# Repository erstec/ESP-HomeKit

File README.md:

# ESP-HomeKit
Espressif ESP-based HomeKit Controller

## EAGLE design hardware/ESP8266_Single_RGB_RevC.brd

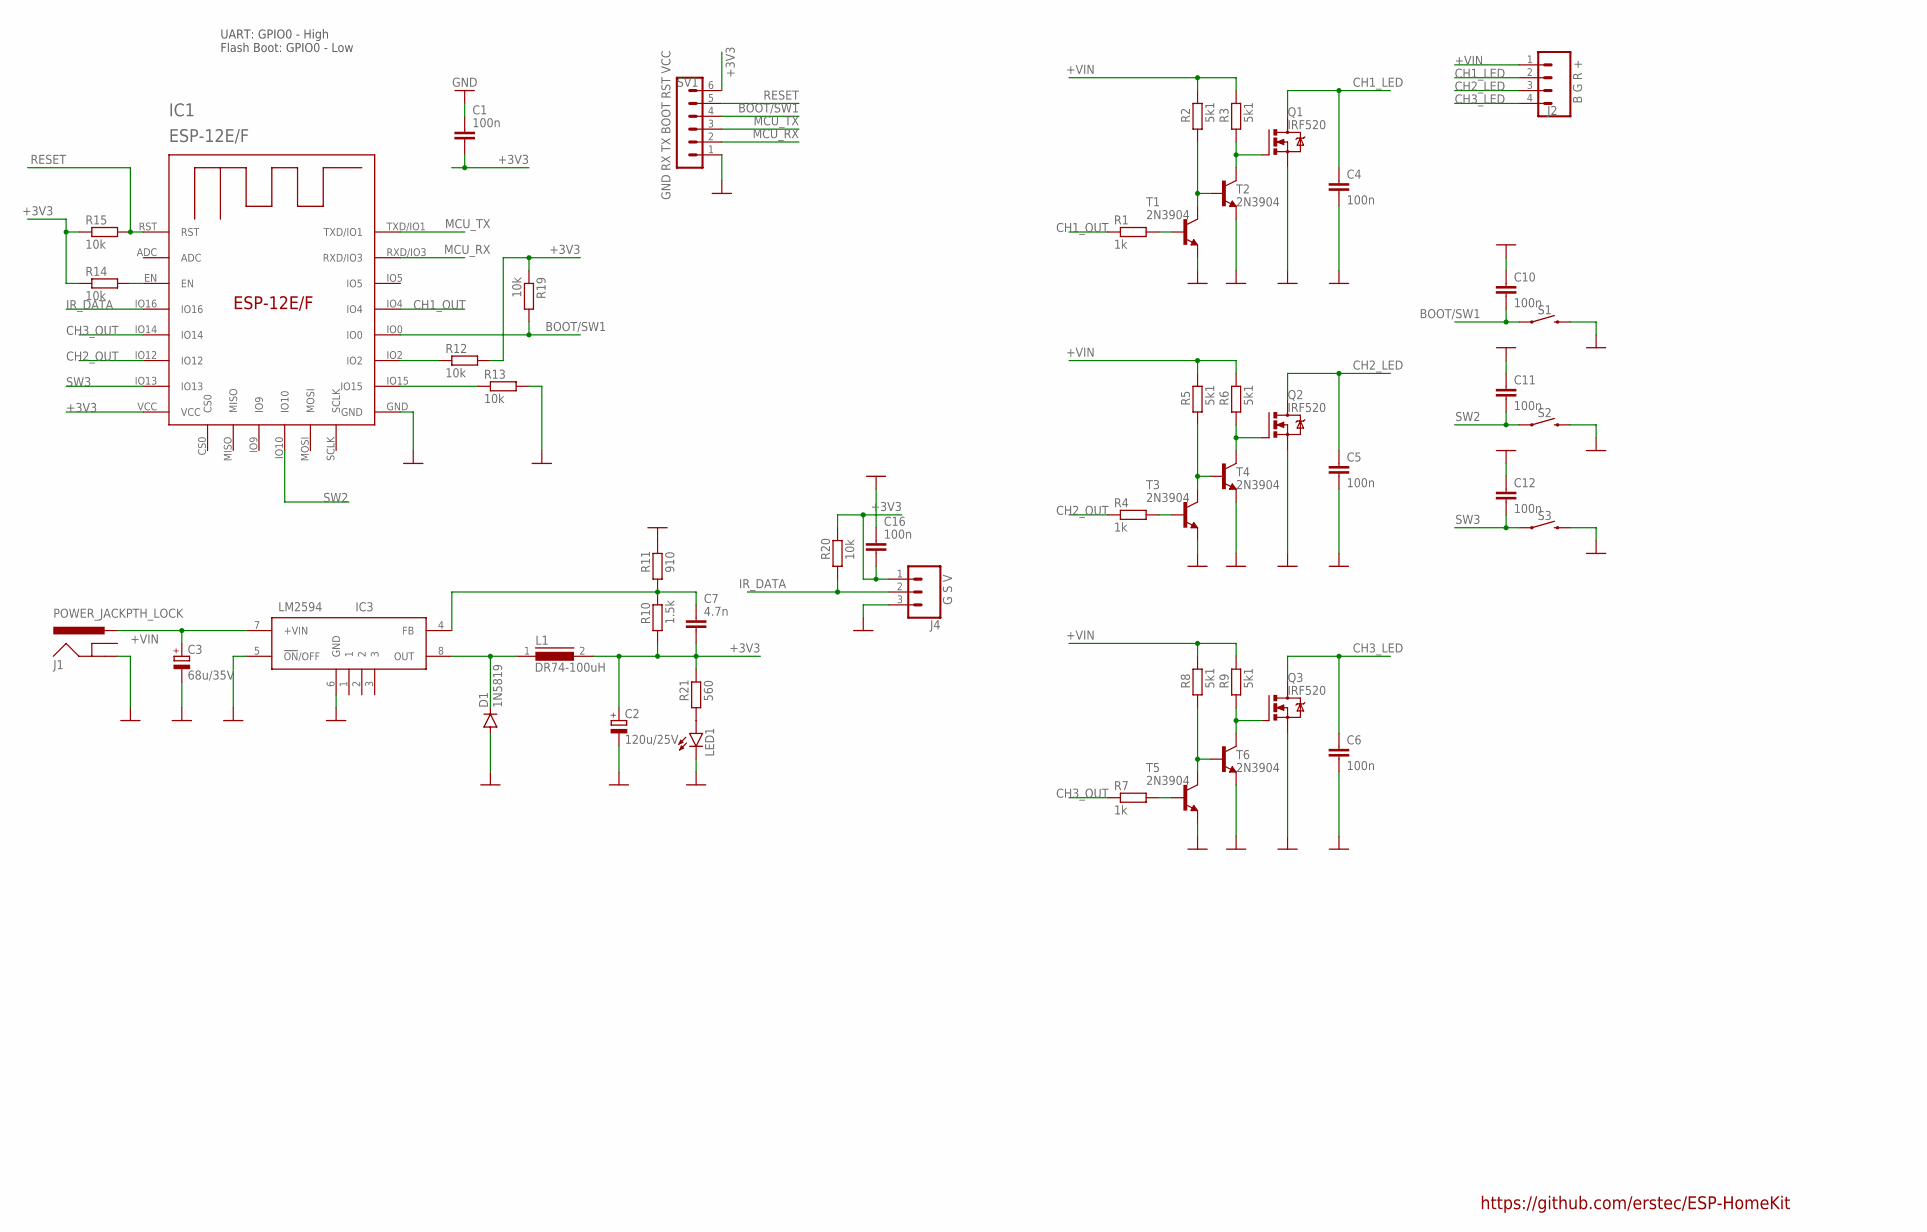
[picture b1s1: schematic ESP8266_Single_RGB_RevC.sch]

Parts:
C1, C4, C5, C6, C10, C11, C12, C16: 100n; C050-024X044
C2: 120u/25V; E2,5-6E
C3: 68u/35V; E2,5-6
C7: 4.7n; C0805
D1: 1N5819; DO41-7.6
IC1: ESP-12E/F; ESP-12E
IC3: LM2594; TSOP8
J1: POWER_JACKPTH_LOCK; POWER_JACK_PTH_LOCK
J2: B G R +; SCREWTERMINAL-3.5MM-4_LOCK
J4: G S V; SCREWTERMINAL-3.5MM-3_LOCK.007S
L1: DR74-100uH; DR74
LED1: LED5MM
Q1, Q2, Q3: IRF520; TO220BV
R1, R4, R7: 1k; 0204/7
R2, R3, R5, R6, R8, R9: 5k1; 0204/7
R10: 1.5k; M0805
R11: 910; R0805
R12, R13, R14, R15, R19, R20: 10k; 0204/7
R21: 560; 0204/7
S1, S2, S3: MOMENTARY-SWITCH-SPST-PTH-6.0MM; TACTILE_SWITCH_PTH_6.0MM
SV1: GND RX TX BOOT RST VCC; MA06-1
T1, T2, T3, T4, T5, T6: 2N3904; TO92-EBC

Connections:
+3V3: C1.2, C2.+, C7.2, C16.2, IC1.VCC, J4.1, L1.2, R10.1, R12.2, R14.1, R15.1, R19.1, R20.2, R21.2, SV1.6
+VIN: C3.+, IC3.7 (+VIN), J1.PWR, J2.1, R2.2, R3.2, R5.2, R6.2, R8.2, R9.2
BOOT/SW1: C10.2, IC1.IO0, R19.2, S1.1, SV1.4
CH1_LED: C4.1, J2.2, Q1.D
CH1_OUT: IC1.IO4, R1.1
CH2_LED: C5.1, J2.3, Q2.D
CH2_OUT: IC1.IO12, R4.1
CH3_LED: C6.1, J2.4, Q3.D
CH3_OUT: IC1.IO14, R7.1
GND: C1.1, C2.-, C3.-, C4.2, C5.2, C6.2, C10.1, C11.1, C12.1, C16.1, D1.A, IC1.GND, IC3.5 (!ON!/OFF), IC3.6 (GND), J1.GND, J4.3, LED1.K (C), Q1.S, Q2.S, Q3.S, R11.2, R13.2, S1.3 (2), S2.3 (2), S3.3 (2), SV1.1, T1.E, T2.E, T3.E, T4.E, T5.E, T6.E
IR_DATA: IC1.IO16, J4.2, R20.1
MCU_RX: IC1.RXD/IO3, SV1.2
MCU_TX: IC1.TXD/IO1, SV1.3
unnamed: R2.1, T1.C, T2.B
unnamed: R1.2, T1.B
unnamed: LED1.A, R21.1
unnamed: Q1.G, R3.1, T2.C
unnamed: C7.1, IC3.4 (FB), R10.2, R11.1
unnamed: R5.1, T3.C, T4.B
unnamed: R4.2, T3.B
unnamed: Q2.G, R6.1, T4.C
unnamed: D1.C, IC3.8 (OUT), L1.1
unnamed: R8.1, T5.C, T6.B
unnamed: R7.2, T5.B
unnamed: Q3.G, R9.1, T6.C
unnamed: IC1.IO2, R12.1
unnamed: IC1.IO15, R13.1
unnamed: IC1.EN, R14.2
RESET: IC1.RST, R15.2, SV1.5
SW2: C11.2, IC1.IO10, S2.1
SW3: C12.2, IC1.IO13, S3.1

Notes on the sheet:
UART: GPIO0 - High Flash Boot: GPIO0 - Low
https://github.com/erstec/ESP-HomeKit

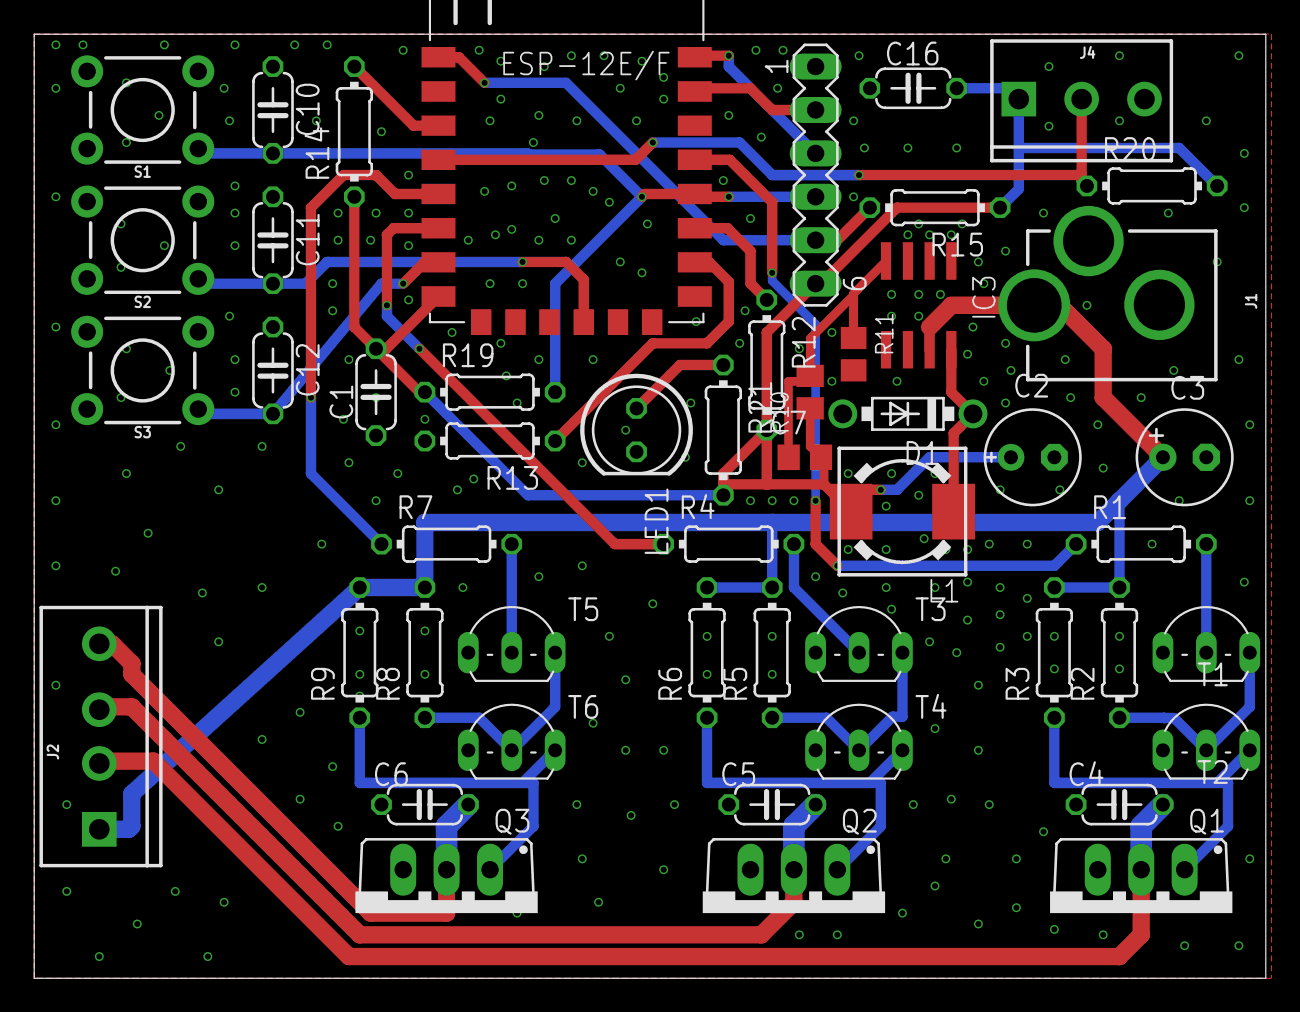
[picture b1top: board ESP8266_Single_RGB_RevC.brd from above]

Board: 2 copper layers, 72.1 x 55.2 mm, 50 parts (0 on the bottom side), 31 nets.

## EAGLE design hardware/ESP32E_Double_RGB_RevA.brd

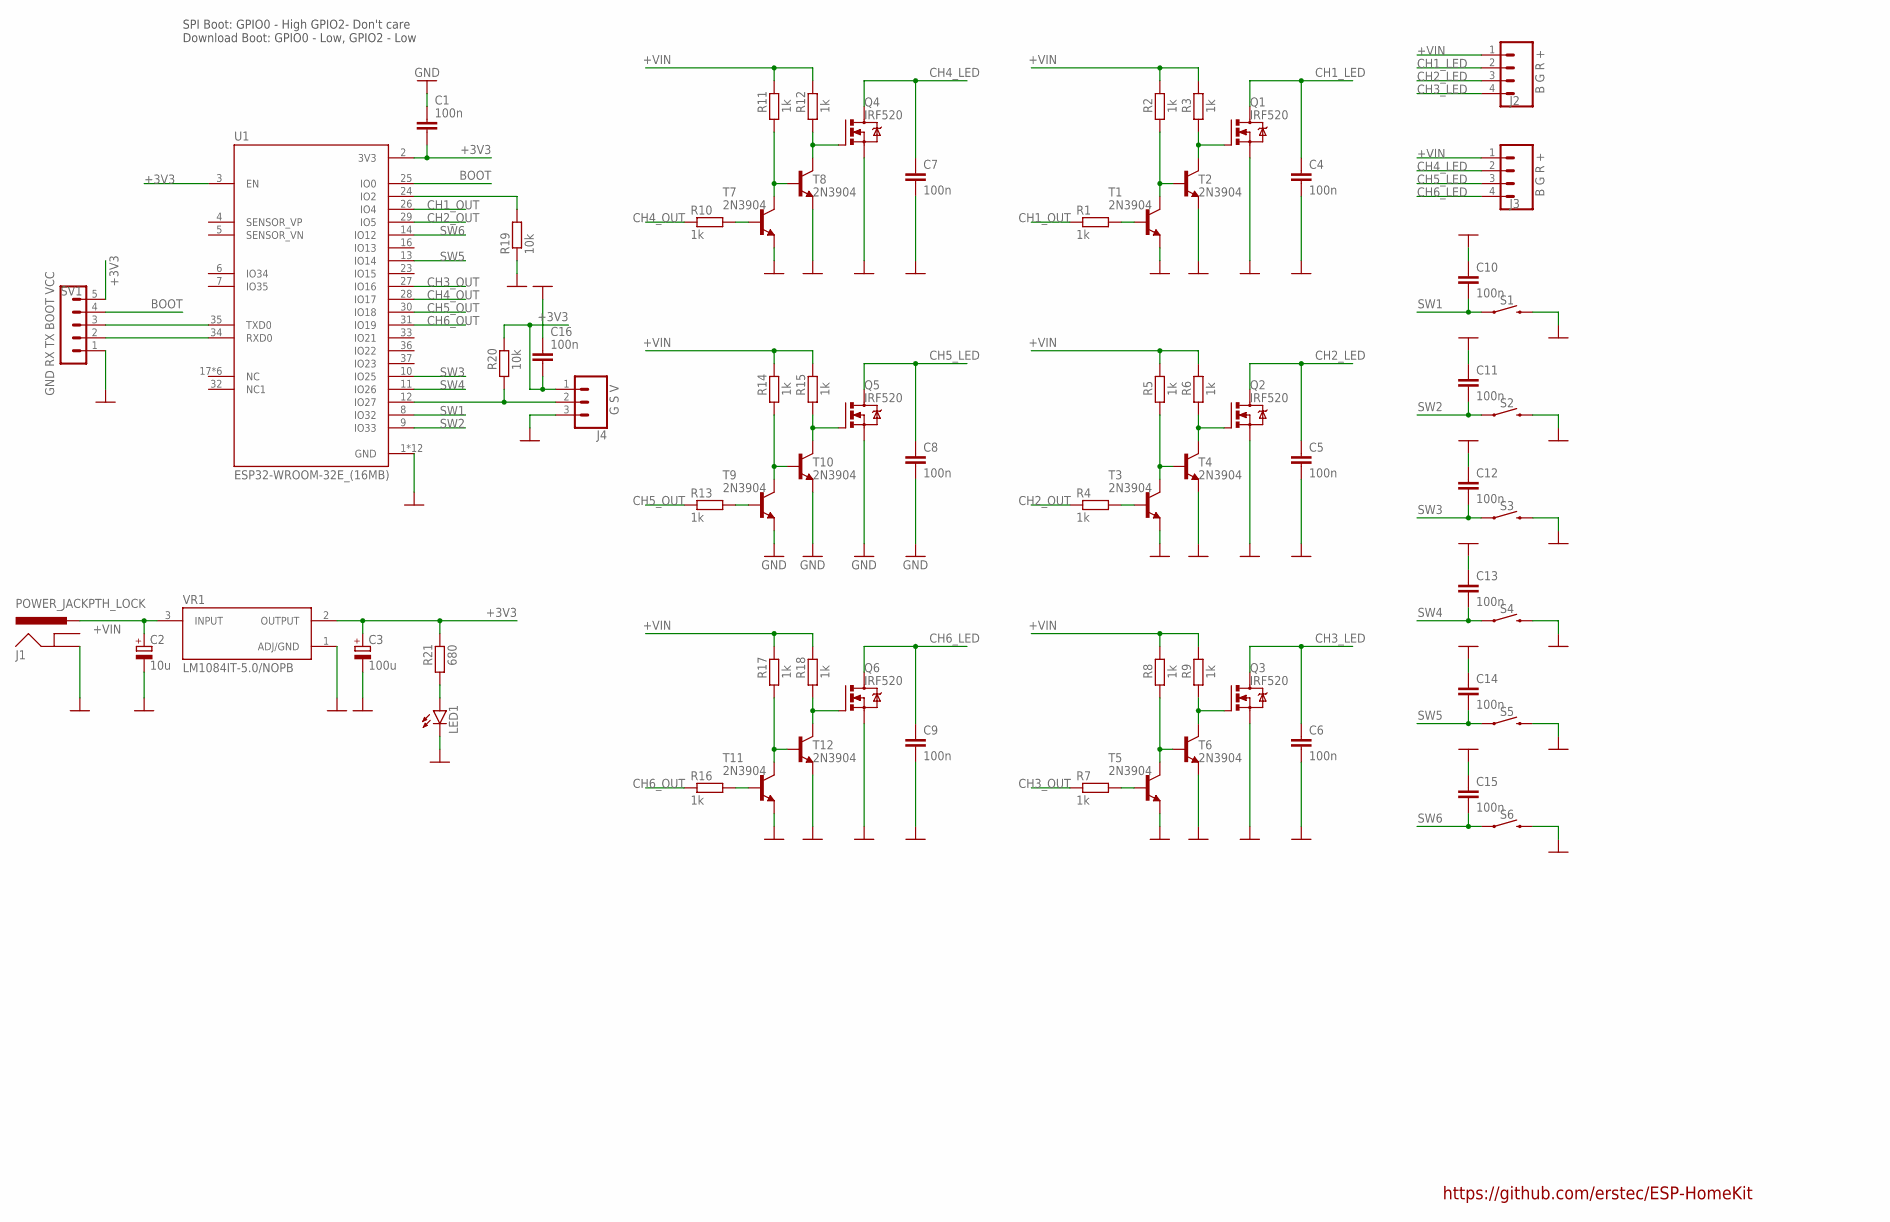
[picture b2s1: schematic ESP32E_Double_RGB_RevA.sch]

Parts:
C1, C4, C5, C6, C7, C8, C9, C10, C11, C12, C13, C14, C15, C16: 100n; C025-024X044
C2: 10u; E2,5-6E
C3: 100u; E2,5-6
J1: POWER_JACKPTH_LOCK; POWER_JACK_PTH_LOCK
J2, J3: B G R +; SCREWTERMINAL-3.5MM-4_LOCK
J4: G S V; SCREWTERMINAL-3.5MM-3_LOCK.007S
LED1: LED5MM
Q1, Q2, Q3, Q4, Q5, Q6: IRF520; TO220BV
R1, R2, R3, R4, R5, R6, R7, R8, R9, R10, R11, R12, R13, R14, R15, R16, R17, R18: 1k; 0207/10
R19, R20: 10k; 0207/10
R21: 680; 0207/10
S1, S2, S3, S4, S5, S6: MOMENTARY-SWITCH-SPST-PTH-6.0MM; TACTILE_SWITCH_PTH_6.0MM
SV1: GND RX TX BOOT VCC; MA05-1
T1, T2, T3, T4, T5, T6, T7, T8, T9, T10, T11, T12: 2N3904; TO92
U1: ESP32-WROOM-32E_(16MB); XCVR_ESP32-WROOM-32E_(16MB)
VR1: LM1084IT-5.0/NOPB; TO254P1054X470X1955-3

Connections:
+3V3: C1.2, C3.+, C16.2, J4.1, R20.2, R21.2, SV1.5, U1.2 (3V3), U1.3 (EN), VR1.2 (OUTPUT)
+VIN: C2.+, J1.PWR, J2.1, J3.1, R2.2, R3.2, R5.2, R6.2, R8.2, R9.2, R11.2, R12.2, R14.2, R15.2, R17.2, R18.2, VR1.3 (INPUT)
BOOT: SV1.4, U1.25 (IO0)
CH1_LED: C4.1, J2.2, Q1.D
CH1_OUT: R1.1, U1.26 (IO4)
CH2_LED: C5.1, J2.3, Q2.D
CH2_OUT: R4.1, U1.29 (IO5)
CH3_LED: C6.1, J2.4, Q3.D
CH3_OUT: R7.1, U1.27 (IO16)
CH4_LED: C7.1, J3.2, Q4.D
CH4_OUT: R10.1, U1.28 (IO17)
CH5_LED: C8.1, J3.3, Q5.D
CH5_OUT: R13.1, U1.30 (IO18)
CH6_LED: C9.1, J3.4, Q6.D
CH6_OUT: R16.1, U1.31 (IO19)
GND: C1.1, C2.-, C3.-, C4.2, C5.2, C6.2, C7.2, C8.2, C9.2, C10.1, C11.1, C12.1, C13.1, C14.1, C15.1, C16.1, J1.GND, J4.3, LED1.K (C), Q1.S, Q2.S, Q3.S, Q4.S, Q5.S, Q6.S, R19.1, S1.3 (2), S2.3 (2), S3.3 (2), S4.3 (2), S5.3 (2), S6.3 (2), SV1.1, T1.3 (E), T2.3 (E), T3.3 (E), T4.3 (E), T5.3 (E), T6.3 (E), T7.3 (E), T8.3 (E), T9.3 (E), T10.3 (E), T11.3 (E), T12.3 (E), U1.1 (GND), U1.15 (GND), U1.38 (GND), U1.39_1 (GND), U1.39_2 (GND), U1.39_3 (GND), U1.39_4 (GND), U1.39_5 (GND), U1.39_6 (GND), U1.39_7 (GND), U1.39_8 (GND), U1.39_9 (GND), VR1.1 (ADJ/GND)
unnamed: R2.1, T1.1 (C), T2.2 (B)
unnamed: R1.2, T1.2 (B)
unnamed: LED1.A, R21.1
unnamed: Q1.G, R3.1, T2.1 (C)
unnamed: J4.2, R20.1, U1.12 (IO27)
unnamed: SV1.2, U1.34 (RXD0)
unnamed: SV1.3, U1.35 (TXD0)
unnamed: R5.1, T3.1 (C), T4.2 (B)
unnamed: R4.2, T3.2 (B)
unnamed: Q2.G, R6.1, T4.1 (C)
unnamed: R8.1, T5.1 (C), T6.2 (B)
unnamed: R7.2, T5.2 (B)
unnamed: Q3.G, R9.1, T6.1 (C)
unnamed: R11.1, T7.1 (C), T8.2 (B)
unnamed: R10.2, T7.2 (B)
unnamed: Q4.G, R12.1, T8.1 (C)
unnamed: R14.1, T9.1 (C), T10.2 (B)
unnamed: R13.2, T9.2 (B)
unnamed: Q5.G, R15.1, T10.1 (C)
unnamed: R17.1, T11.1 (C), T12.2 (B)
unnamed: R16.2, T11.2 (B)
unnamed: Q6.G, R18.1, T12.1 (C)
unnamed: R19.2, U1.24 (IO2)
SW1: C10.2, S1.1, U1.8 (IO32)
SW2: C11.2, S2.1, U1.9 (IO33)
SW3: C12.2, S3.1, U1.10 (IO25)
SW4: C13.2, S4.1, U1.11 (IO26)
SW5: C14.2, S5.1, U1.13 (IO14)
SW6: C15.2, S6.1, U1.14 (IO12)

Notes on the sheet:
SPI Boot: GPIO0 - High GPIO2- Don't care Download Boot: GPIO0 - Low, GPIO2 - Low
https://github.com/erstec/ESP-HomeKit

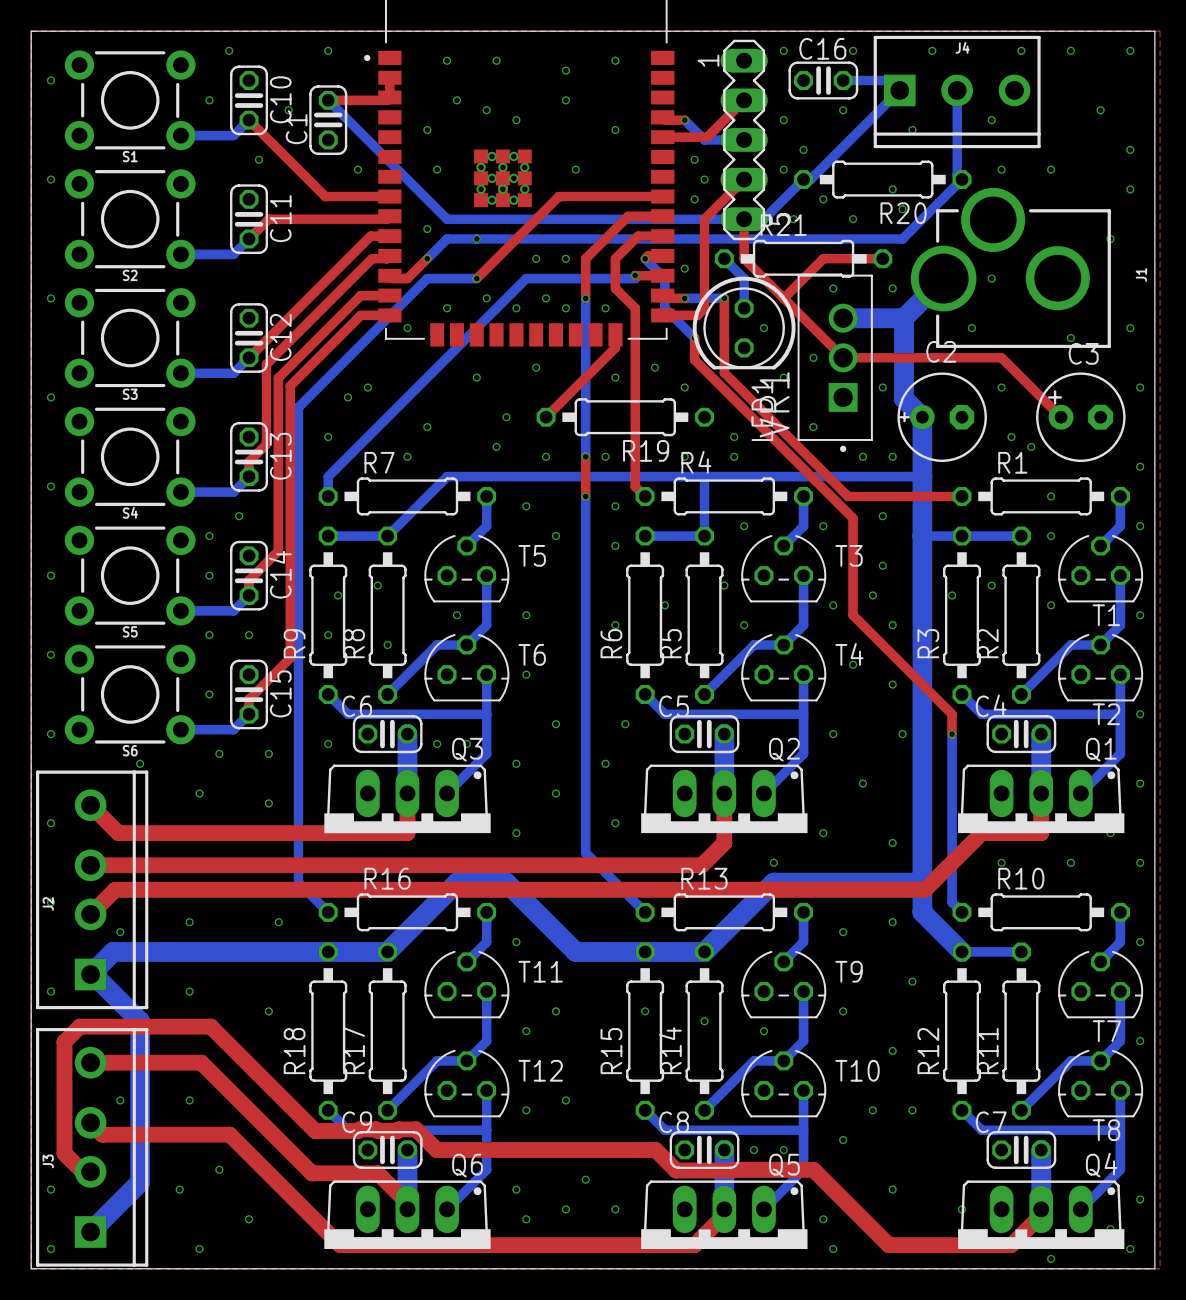
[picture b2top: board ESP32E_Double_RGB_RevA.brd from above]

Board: 2 copper layers, 72.1 x 79.4 mm, 69 parts (0 on the bottom side), 45 nets.

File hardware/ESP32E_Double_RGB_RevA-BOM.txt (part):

Partlist exported from C:/_repo/_fw/ESP-HomeKit/hardware/ESP32E_Double_RGB_RevA.sch at 2022-12-03 19:31

Qty Value                           Device                          Package                         Parts                                                                           Description                                                                                                     AVAILABILITY DESCRIPTION                                                                                                                             MF                MP                     MPN OC_FARNELL OC_NEWARK PACKAGE                    POPULARITY PRICE PROD_ID     PURCHASE-URL                                                       SF_ID     SF_SKU    SPICEPREFIX
1                                   LED5MM                          LED5MM                          LED1                                                                            LED                                                                                                                                                                                                                                                                                                                                                               93                                                                                                                             
14  100n                            C-EU025-024X044                 C025-024X044                    C1, C4, C5, C6, C7, C8, C9, C10, C11, C12, C13, C14, C15, C16                   CAPACITOR, European symbol                                                                                                                                                                                                                                                                                                                                        56                                                                                                                  C          
1   100u                            CPOL-EUE2.5-6                   E2,5-6                          C3                                                                              POLARIZED CAPACITOR, European symbol                                                                                                                                                                                                                                                                                                                              26                                                                                                                  C          
2   10k                             R-EU_0207/10                    0207/10                         R19, R20                                                                        RESISTOR, European symbol                                                                                                                                                                                                                                                                                                                                         81                                                                                                                  R          
1   10u                             CPOL-EUE2,5-6E                  E2,5-6E                         C2                                                                              POLARIZED CAPACITOR, European symbol                                                                                                                                                                                                                                                                                                                              27                                                                                                                  C          
18  1k                              R-EU_0207/10                    0207/10                         R1, R2, R3, R4, R5, R6, R7, R8, R9, R10, R11, R12, R13, R14, R15, R16, R17, R18 RESISTOR, European symbol                                                                                                                                                                                                                                                                                                                                         81                                                                                                                  R          
12  2N3904                          2N3904                          TO92                            T1, T2, T3, T4, T5, T6, T7, T8, T9, T10, T11, T12                               NPN TRANSISTOR                                                                                                                                                                                                                                                                                                                                                    27                                                                                                                             
1   680                             R-EU_0207/10                    0207/10                         R21                                                                             RESISTOR, European symbol                                                                                                                                                                                                                                                                                                                                         81                                                                                                                  R          
2   B G R +                         CONN_04SCREW_LOCK               SCREWTERMINAL-3.5MM-4_LOCK      J2, J3                                                                          Multi connection point. Often used as Generic Header-pin footprint for 0.1 inch spaced/style header connections                                                                                                                                                                                                                                                                                                                                                                                  
1   ESP32-WROOM-32E_(16MB)          ESP32-WROOM-32E_(16MB)          XCVR_ESP32-WROOM-32E_(16MB)     U1                                                                              Check availability                                                                                              Not in stock  Bluetooth, WiFi 802.11b/g/n, Bluetooth v4.2 +EDR, Class 1, 2 and 3 Transceiver Module 2.4GHz ~ 2.5GHz Integrated, Trace Surface Mount  Espressif Systems ESP32-WROOM-32E (16MB)                          None                                  None                                                                                                                
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
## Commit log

2022-12-03 Added Hardware RevA
2022-12-03 Added PDF's and PNG's
2022-12-18 porting from https://github.com/erstec/ESP8266-HomeKit-Outlet
2022-12-18 fix R16 - NOT NEEDED at ALL
2022-12-19 RevB of Single started
2022-12-19 RevB more
2022-12-19 lightbulb working draft
2022-12-19 RGB LED draft
2022-12-19 PWM freq up 1kHz -> 25 kHz
2022-12-20 ESP8266 Single RevB fixed, Gerbers added
2022-12-29 Added Rev C
2022-12-30 RevC Ok

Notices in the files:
parts and their libraries:
SparkFun-Connectors: Licensing: Creative Commons ShareAlike 4.0 International - https://creativecommons.org/licenses/by-sa/4.0
